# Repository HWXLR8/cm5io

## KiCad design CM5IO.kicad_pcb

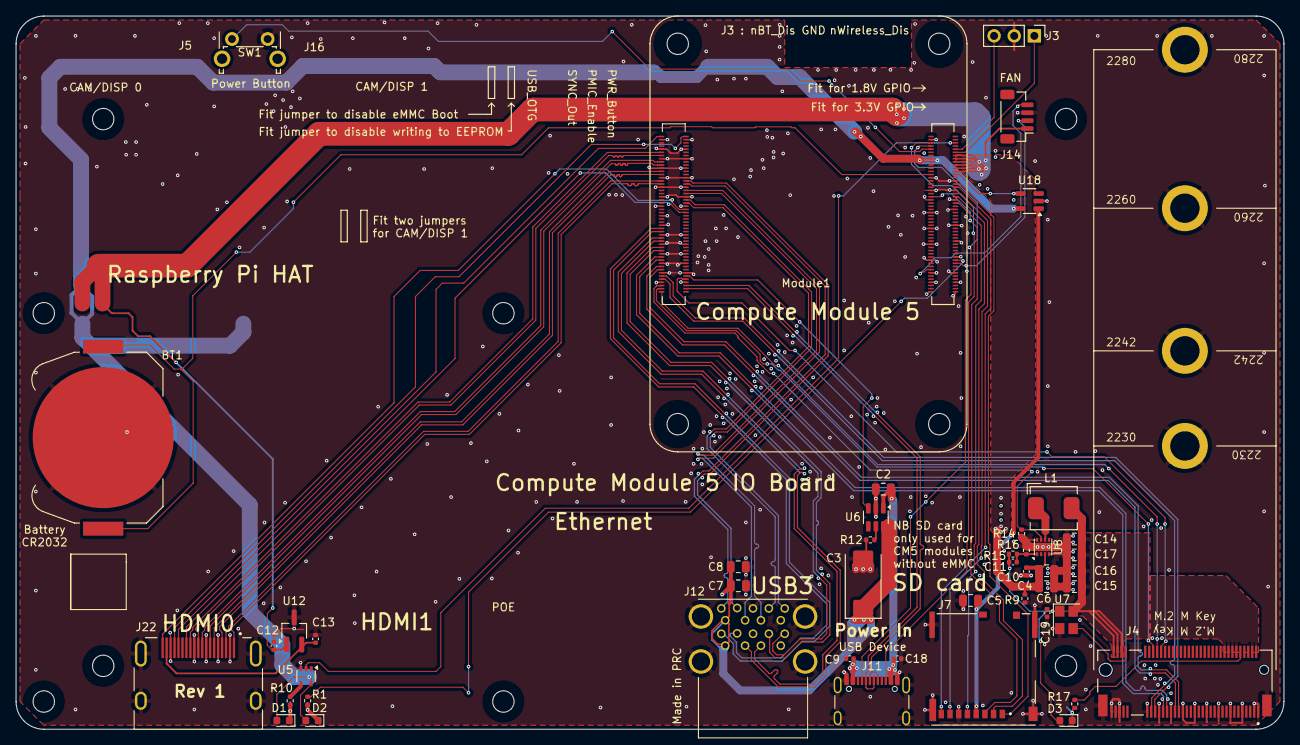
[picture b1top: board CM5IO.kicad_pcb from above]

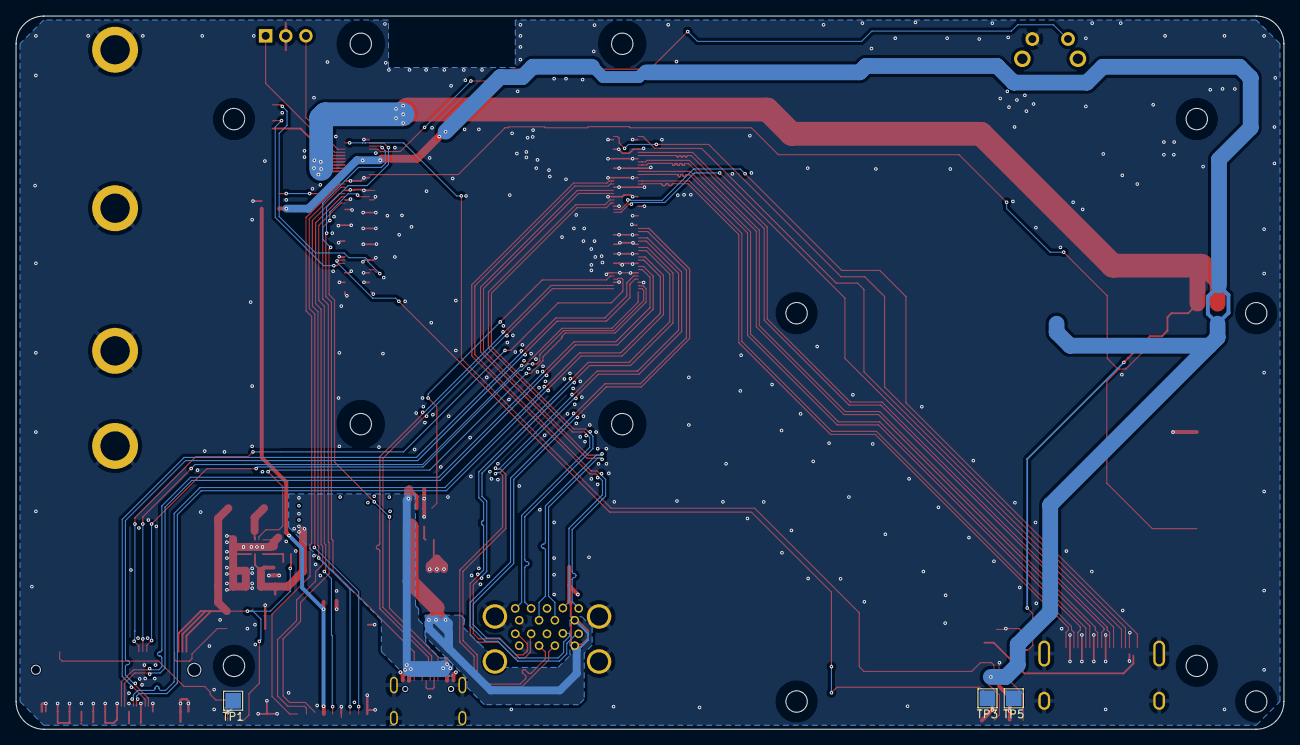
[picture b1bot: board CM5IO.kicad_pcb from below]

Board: 4 copper layers, 160.0 x 90.0 mm, 57 parts (3 on the bottom side), 71 nets.

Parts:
BT1: Battery_Cell; BatteryHolder_Keystone_3034_1x20mm
C2, C4, C5, C6, C7, C8, C14, C15, C16, C17: 10u; C_0805_2012Metric
C3: 100uF; CP_EIA-7343-31_Kemet-D
C9, C10, C12, C13, C18, C19: 100n; C_0402_1005Metric
C11: 4.7nF; C_0402_1005Metric
D1: LED Red; LED_0603_1608Metric
D2, D3: LED Green; LED_0603_1608Metric
H1, H2, H3, H4, H5, H6, H7, H8: MountingHole; MountingHole_2.7mm_M2.5_DIN965
J3: Conn_01x03; PinHeader_1x03_P2.54mm_Vertical
J4: Bus_M.2_Socket_M; M.2 M Key socket
J7: Micro_SD_Card_Det; SDCARD_MOLEX_503398-1892
J11: USB_C_Receptacle_USB2.0; USB_C_Receptacle_GCT_USB4105-xx-A_16P_TopMnt_Horizontal
J12: USB3_A; MTCONN_UBAF30-D2011
J14: JST_SHBM04B-SRSS-TB; JST_SH_BM04B-SRSS-TB_1x04-1MP_P1.00mm_Vertical
J22: 690-019-298-412; EDAC 690-019-298-412
L1: 2.2uH; L_Bourns_SRP5030CC
Module1: ComputeModule5-CM5; Raspberry-Pi-5-Compute-Module
R1, R10, R17: 1k; R_0402_1005Metric
R9, R16: 2.2K 1%; R_0402_1005Metric
R12: 15K 1%; R_0402_1005Metric
R14: 100K 1%; R_0402_1005Metric
R15: 10K 1%; R_0402_1005Metric
SW1: Right angle Tact button; SW_Tactile_SPST_Angled_PTS645Vx58-2LFS
TP1, TP3, TP5: TestPoint; TestPoint_Pad_2.0x2.0mm
U5: 74LVC1G07SE-7; SOT-353_SC-70-5
U6: AP22653W6; SOT-23-6
U7: ASEK-32.768KHZ-L-R-T; Crystal_SMD_3225-4Pin_3.2x2.5mm
U8: AP3441SHE-7B; DFN-8-1EP_2x2mm_P0.5mm_EP1.05x1.75mm
U12: RT9742SNGV; TSOT-23_HandSoldering
U18: RT9742GGJ5; SOT-23-5

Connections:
/+3.3v: D1.2 (A), D2.2 (A), Module1.84 (+3.3v_(Output)), Module1.86 (+3.3v_(Output)), U5.5 (VCC), U18.5 (IN)
/+5v: C2.1, C4.1, C6.1, C9.1, C10.1, C12.1, C18.1, J11.A4 (VBUS), J11.A9 (VBUS), J11.B4 (VBUS), J11.B9 (VBUS), J14.1, Module1.77 (+5v_(Input)), Module1.79 (+5v_(Input)), Module1.81 (+5v_(Input)), Module1.83 (+5v_(Input)), Module1.85 (+5v_(Input)), Module1.87 (+5v_(Input)), R9.1, U6.1 (IN), U8.3 (VIN), U12.1 (IN)
/CC1: J11.A5 (CC1), Module1.94 (CC1)
/CC2: J11.B5 (CC2), Module1.96 (CC2)
/CM5_GPIO ( Ethernet, GPIO, SDCARD)/+1.8v: Module1.88 (+1.8v_(Output)), Module1.90 (+1.8v_(Output))
/CM5_GPIO ( Ethernet, GPIO, SDCARD)/BT_nDis: J3.3, Module1.91 (BT_nDisable)
/CM5_GPIO ( Ethernet, GPIO, SDCARD)/PWM: J14.2, Module1.19 (FAN_PWM)
/CM5_GPIO ( Ethernet, GPIO, SDCARD)/PWR_BUT: Module1.92 (PWR_BUT), SW1.1
/CM5_GPIO ( Ethernet, GPIO, SDCARD)/SD_CLK: J7.5 (CLK), Module1.57 (SD_CLK)
/CM5_GPIO ( Ethernet, GPIO, SDCARD)/SD_CMD: J7.3 (CMD), Module1.62 (SD_CMD)
/CM5_GPIO ( Ethernet, GPIO, SDCARD)/SD_DAT0: J7.7 (DAT0), Module1.63 (SD_DAT0)
/CM5_GPIO ( Ethernet, GPIO, SDCARD)/SD_DAT1: J7.8 (DAT1), Module1.67 (SD_DAT1)
/CM5_GPIO ( Ethernet, GPIO, SDCARD)/SD_DAT2: J7.1 (DAT2), Module1.69 (SD_DAT2)
/CM5_GPIO ( Ethernet, GPIO, SDCARD)/SD_DAT3: J7.2 (DAT3/CD), Module1.61 (SD_DAT3)
/CM5_GPIO ( Ethernet, GPIO, SDCARD)/SD_PWR: C5.1, J7.4 (VDD), U18.1 (OUT)
/CM5_GPIO ( Ethernet, GPIO, SDCARD)/SD_PWR_ON: Module1.75 (SD_PWR_ON), U18.4 (EN)
/CM5_GPIO ( Ethernet, GPIO, SDCARD)/TACHO: J14.4, Module1.16 (FAN_TACHO)
/CM5_GPIO ( Ethernet, GPIO, SDCARD)/VBAT: BT1.1 (+), Module1.76 (VBAT)
/CM5_GPIO ( Ethernet, GPIO, SDCARD)/WL_nDis: J3.1, Module1.89 (WiFi_nDisable)
/CM5_GPIO ( Ethernet, GPIO, SDCARD)/nPWR_LED: Module1.95 (LED_nPWR), U5.2
/CM5_HighSpeed/HDMI0_CEC: J22.13 (CEC), Module1.151 (HDMI0_CEC)
/CM5_HighSpeed/HDMI0_CK_N: J22.12 (CK-), Module1.190 (HDMI0_CLK_N)
/CM5_HighSpeed/HDMI0_CK_P: J22.10 (CK+), Module1.188 (HDMI0_CLK_P)
/CM5_HighSpeed/HDMI0_D0_N: J22.9 (D0-), Module1.184 (HDMI0_TX0_N)
/CM5_HighSpeed/HDMI0_D0_P: J22.7 (D0+), Module1.182 (HDMI0_TX0_P)
/CM5_HighSpeed/HDMI0_D1_N: J22.6 (D1-), Module1.178 (HDMI0_TX1_N)
/CM5_HighSpeed/HDMI0_D1_P: J22.4 (D1+), Module1.176 (HDMI0_TX1_P)
/CM5_HighSpeed/HDMI0_D2_N: J22.3 (D2-), Module1.172 (HDMI0_TX2_N)
/CM5_HighSpeed/HDMI0_D2_P: J22.1 (D2+), Module1.170 (HDMI0_TX2_P)
/CM5_HighSpeed/HDMI0_HOTPLUG: J22.19 (HPD/HEAC-), Module1.153 (HDMI0_HOTPLUG)
/CM5_HighSpeed/HDMI0_SCL: J22.15 (SCL), Module1.200 (HDMI0_SCL)
/CM5_HighSpeed/HDMI0_SDA: J22.16 (SDA), Module1.199 (HDMI0_SDA)
/CM5_HighSpeed/HDMI_5v: C13.1, J22.18 (+5V), U12.2 (OUT)
/CM5_HighSpeed/PCIE_CLK_N: J4.53 (REFCLKn), Module1.112 (PCIe_CLK_N)
/CM5_HighSpeed/PCIE_CLK_P: J4.55 (REFCLKp), Module1.110 (PCIe_CLK_P)
/CM5_HighSpeed/PCIE_PWR_EN: Module1.106 (PCIE_PWR_EN), R14.1, U8.7 (EN)
/CM5_HighSpeed/PCIE_RX_N: J4.43 (PETp0), Module1.118 (PCIe_RX_N)
/CM5_HighSpeed/PCIE_RX_P: J4.41 (PETn0), Module1.116 (PCIe_RX_P)
/CM5_HighSpeed/PCIE_TX_N: J4.49 (PERp0), Module1.124 (PCIe_TX_N)
/CM5_HighSpeed/PCIE_TX_P: J4.47 (PERn0), Module1.122 (PCIe_TX_P)
/CM5_HighSpeed/PCIE_nCLKREQ: J4.52 (~CLKREQ), Module1.102 (PCIe_nCLKREQ)
/CM5_HighSpeed/PCIE_nRST: J4.50 (~PERST), Module1.109 (PCIe_nRST)
/CM5_HighSpeed/PCIE_nWAKE: J4.54 (~PEWAKE), Module1.104 (PCIE_nWAKE)
/CM5_HighSpeed/USB3-0-D_N: J12.A2 (D-), Module1.136 (USB3-0-D_N)
/CM5_HighSpeed/USB3-0-D_P: J12.A3 (D+), Module1.134 (USB3-0-D_P)
/CM5_HighSpeed/USB3-0-RX_N: J12.A6 (SSRX+), Module1.128 (USB3-0-RX_N)
/CM5_HighSpeed/USB3-0-RX_P: J12.A5 (SSRX-), Module1.130 (USB3-0-RX_P)
/CM5_HighSpeed/USB3-0-TX_N: J12.A9 (SSTX+), Module1.140 (USB3-0-TX_N)
/CM5_HighSpeed/USB3-0-TX_P: J12.A8 (SSTX-), Module1.142 (USB3-0-TX_P)
/CM5_HighSpeed/USB3-1-D_N: J12.B2 (D-), Module1.165 (USB3-1-D_N)
/CM5_HighSpeed/USB3-1-D_P: J12.B3 (D+), Module1.163 (USB3-1-D_P)
/CM5_HighSpeed/USB3-1-RX_N: J12.B6 (SSRX+), Module1.157 (USB3-1-RX_N)
/CM5_HighSpeed/USB3-1-RX_P: J12.B5 (SSRX-), Module1.159 (USB3-1-RX_P)
/CM5_HighSpeed/USB3-1-TX_N: J12.B9 (SSTX+), Module1.169 (USB3-1-TX_N)
/CM5_HighSpeed/USB3-1-TX_P: J12.B8 (SSTX-), Module1.171 (USB3-1-TX_P)
/CM5_HighSpeed/VBUS: C3.1, C7.1, C8.1, J12.A1 (VBUS), J12.B1 (VBUS), U6.6 (OUT)
/CM5_HighSpeed/VBUS_EN: Module1.111 (VBUS_EN), U6.3 (EN)
/PCIe-M2/FB: C11.2, R15.2, R16.1, U8.1 (FB)
/PCIe-M2/M2_3v3: C11.1, C14.1, C15.1, C16.1, C17.1, C19.1, D3.2 (A), J4.2 (3.3V), J4.4 (3.3V), J4.12 (3.3V), J4.14 (3.3V), J4.16 (3.3V), J4.18 (3.3V), J4.70 (3.3V), J4.72 (3.3V), J4.74 (3.3V), L1.2, R15.1, U7.1 (EN), U7.4 (VDD)
/USB2_N: J11.A7 (D-), J11.B7 (D-), Module1.103 (USB2_N)
/USB2_P: J11.A6 (D+), J11.B6 (D+), Module1.105 (USB2_P)
GND: BT1.2 (-), C2.2, C3.2, C4.2, C5.2, C6.2, C7.2, C8.2, C9.2, C10.2, C12.2, C13.2, C14.2, C15.2, C16.2, C17.2, C18.2, C19.2, J3.2, J4.1 (GND), J4.3 (GND), J4.9 (GND), J4.15 (GND), J4.21 (GND), J4.27 (GND), J4.33 (GND), J4.39 (GND), J4.45 (GND), J4.51 (GND), J4.57 (GND), J4.71 (GND), J4.73 (GND), J4.75 (GND), J4.M1 (GND2230), J4.M2 (GND2242), J4.M3 (GND2260), J4.M4 (GND2280), J4.S1, J4.S2, J7.6 (VSS), J7.11 (SHIELD), J11.A1 (GND), J11.A12 (GND), J11.B1 (GND), J11.B12 (GND), J11.S1 (SHIELD), J12.10 (SHIELD), J12.A4 (GND), J12.A7 (DRAIN), J12.B4 (GND), J12.B7 (DRAIN), J14.3, J22.2 (D2S), J22.5 (D1S), J22.8 (D0S), J22.11 (CKS), J22.17 (GND), J22.SH1 (SH), J22.SH2 (SH), J22.SH3 (SH), J22.SH4 (SH), Module1.1 (GND), Module1.2 (GND), Module1.7 (GND), Module1.8 (GND), Module1.13 (GND), Module1.14 (GND), Module1.22 (GND), Module1.23 (GND), Module1.32 (GND), Module1.33 (GND), Module1.42 (GND), Module1.43 (GND), Module1.52 (GND), Module1.53 (GND), Module1.59 (GND), Module1.60 (GND), Module1.65 (GND), Module1.66 (GND), Module1.71 (GND), Module1.74 (GND), Module1.98 (GND), Module1.107 (GND), Module1.108 (GND), Module1.113 (GND), Module1.114 (GND), Module1.119 (GND), Module1.120 (GND), Module1.125 (GND), Module1.126 (GND), Module1.131 (GND), Module1.132 (GND), Module1.137 (GND), Module1.138 (GND), Module1.144 (GND), Module1.150 (GND), Module1.155 (GND), Module1.156 (GND), Module1.161 (GND), Module1.162 (GND), Module1.167 (GND), Module1.168 (GND), Module1.173 (GND), Module1.174 (GND), Module1.179 (GND), Module1.180 (GND), Module1.185 (GND), Module1.186 (GND), Module1.191 (GND), Module1.192 (GND), Module1.197 (GND), Module1.198 (GND), R9.2, R12.2, R14.2, R16.2, SW1.2, U5.3 (GND), U6.2 (GND), U7.2 (GND), U8.4 (PGND), U8.8 (SGND), U8.9 (PAD), U12.3 (GND), U18.2 (GND)
unnamed: D1.1 (K), R10.1, TP5.1
unnamed: D2.1 (K), R1.1, TP3.1
unnamed: D3.1 (K), R17.1, TP1.1
unnamed: J4.10 (DAS/~DSS/~LED1), R17.2
unnamed: J4.68 (SUSCLK), U7.3 (Out)
unnamed: Module1.21 (LED_nACT), R1.2
unnamed: R10.2, U5.4
unnamed: R12.1, U6.5 (ILIM)
unnamed: L1.1, U8.6 (LX)

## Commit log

2025-06-16 removed most of the things I don't care about. no routing yet.
2025-06-17 remove more components, set stackup to JLC04161H-7628
